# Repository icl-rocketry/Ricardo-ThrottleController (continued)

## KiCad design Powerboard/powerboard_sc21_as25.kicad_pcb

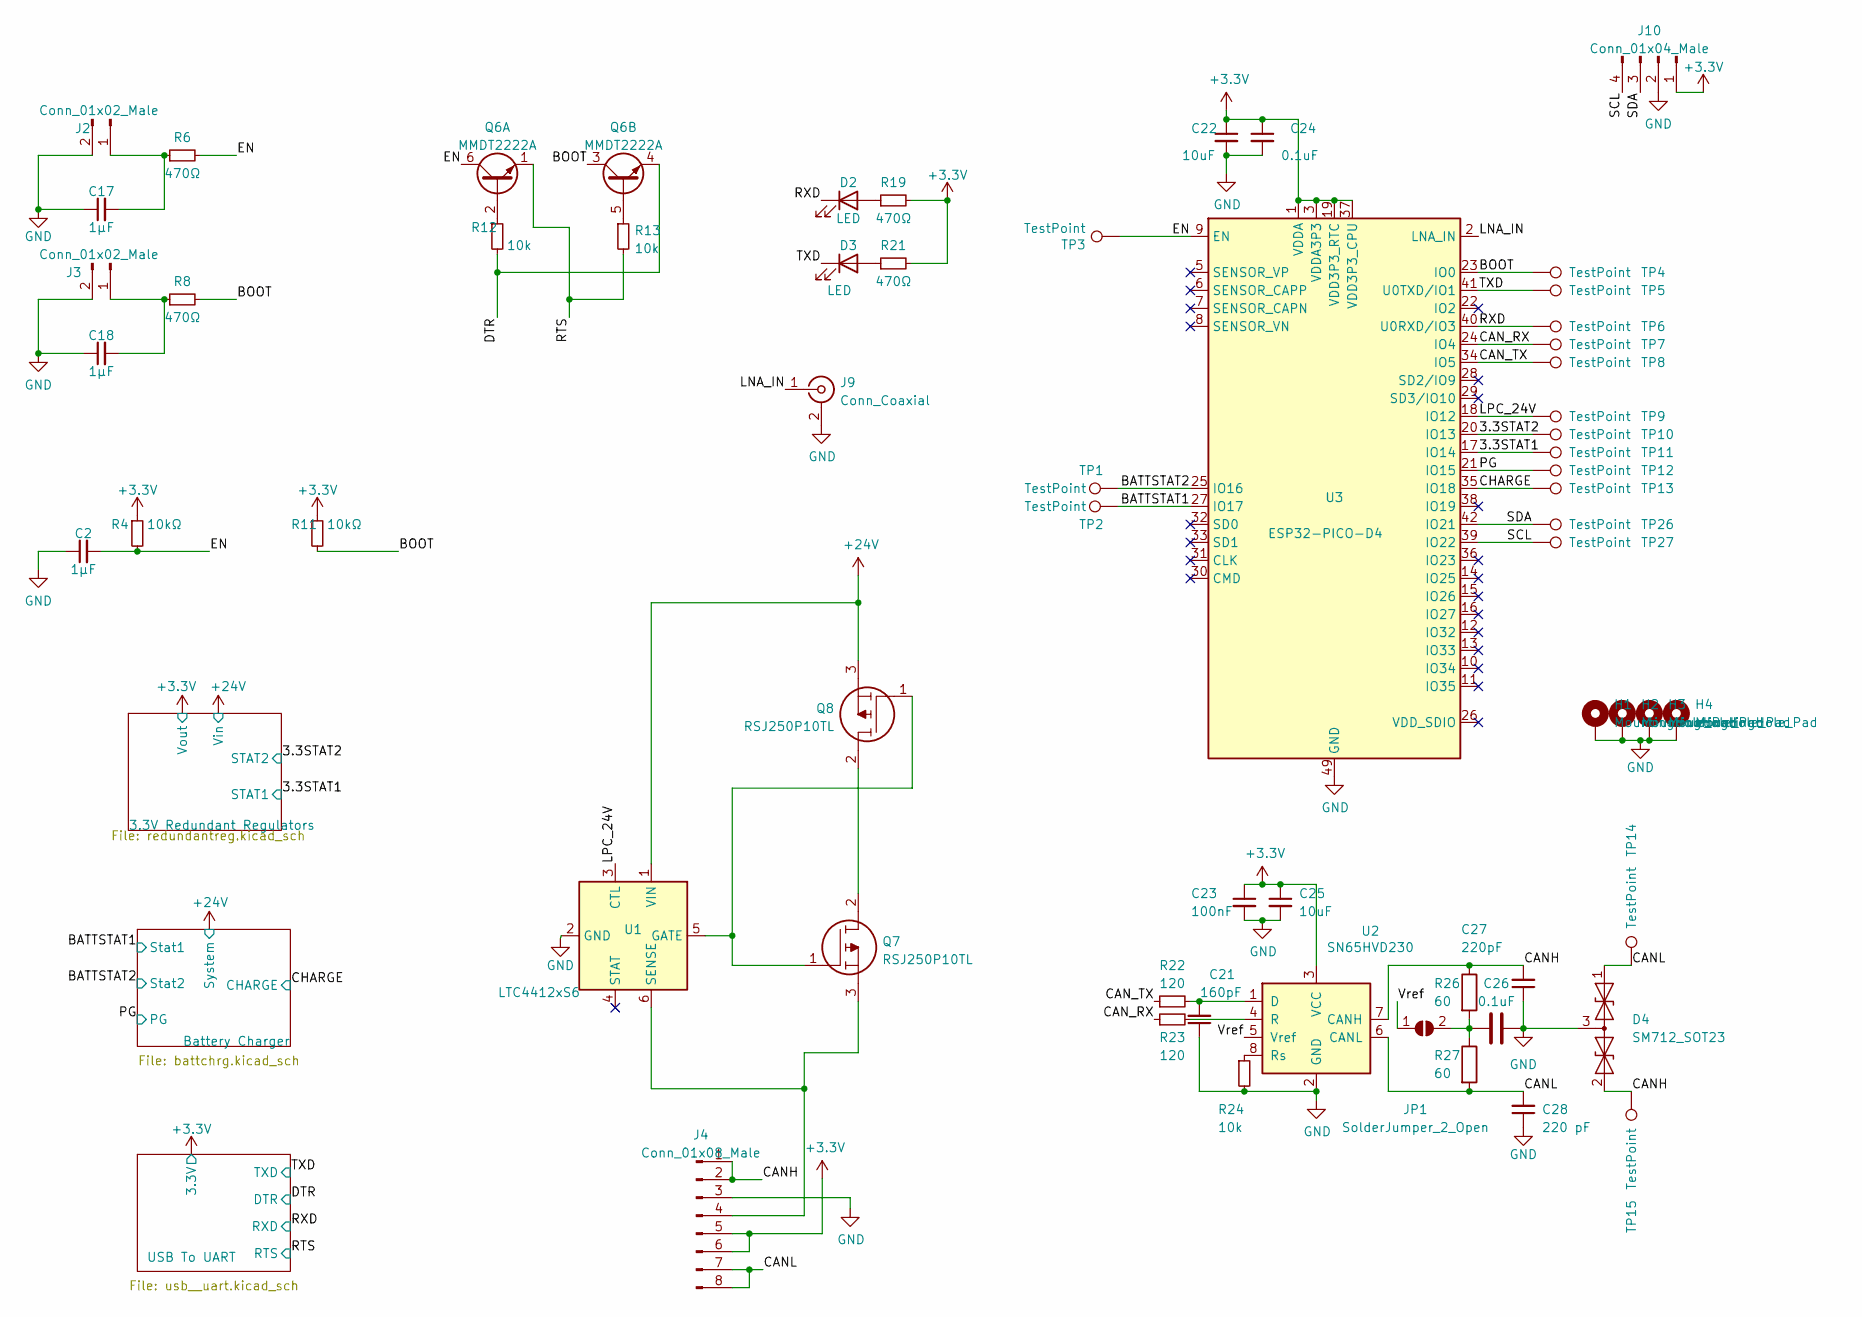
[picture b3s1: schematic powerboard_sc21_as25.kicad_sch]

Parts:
C2, C17, C18: 1μF; C_0603_1608Metric
C21: 160pF; C_0603_1608Metric
C22, C25: 10uF; C_0805_2012Metric
C23: 100nF; C_0603_1608Metric
C24, C26: 0.1uF; C_0603_1608Metric
C27: 220pF; C_0603_1608Metric
C28: 220 pF; C_0603_1608Metric
D2, D3: LED; LED_0603_1608Metric
D4: SM712_SOT23; SOT-23
H1, H2, H3, H4: MountingHole_Pad; MountingHole_3.2mm_M3_DIN965_Pad
J2, J3: Conn_01x02_Male; PinHeader_1x02_P2.54mm_Vertical
J4: Conn_01x08_Male; Molex_Mini-Fit_Jr_5566-08A_2x04_P4.20mm_Vertical
J9: Conn_Coaxial; U.FL_Molex_MCRF_73412-0110_Vertical
J10: Conn_01x04_Male; JST_XH_B4B-XH-AM_1x04_P2.50mm_Vertical
JP1: SolderJumper_2_Open; SolderJumper-2_P1.3mm_Open_RoundedPad1.0x1.5mm
Q6: MMDT2222A; SOT-363_SC-70-6
Q7, Q8: RSJ250P10TL; TO-263-3_TabPin2; Manufacturer_Part_Number RSJ250P10TL; Mouser Part Number 755-RSJ250P10TL
R4, R11: 10kΩ; R_0603_1608Metric
R6, R8, R19, R21: 470Ω; R_0603_1608Metric
R12, R13, R24: 10k; R_0603_1608Metric
R22, R23: 120; R_0603_1608Metric
R26, R27: 60; R_0603_1608Metric
TP1, TP2, TP3, TP4, TP5, TP6, TP7, TP8, TP9, TP10, TP11, TP12, TP13, TP14, TP15, TP26, TP27: TestPoint; TestPoint_Pad_D1.0mm
U1: LTC4412xS6; TSOT-23-6
U2: SN65HVD230; SOIC-8_3.9x4.9mm_P1.27mm
U3: ESP32-PICO-D4; QFN-48-1EP_7x7mm_P0.5mm_EP5.3x5.3mm

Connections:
+3V3: C22.1, C23.1, C24.1, C25.1, J4.5, J4.6, J10.1, R4.1, R11.1, R19.2, R21.2, U2.3 (VCC), U3.1 (VDDA), U3.3 (VDDA3P3), U3.4 (VDDA3P3), U3.19 (VDD3P3_RTC), U3.37 (VDD3P3_CPU), U3.43 (VDDA), U3.46 (VDDA); also elsewhere on the board
+24V: Q8.3, U1.1 (VIN); also elsewhere on the board
/3.3STAT1: TP11.1, U3.17 (IO14); also elsewhere on the board
/3.3STAT2: TP10.1, U3.20 (IO13); also elsewhere on the board
/BATTSTAT1: TP2.1, U3.27 (IO17); also elsewhere on the board
/BATTSTAT2: TP1.1, U3.25 (IO16); also elsewhere on the board
/BOOT: Q6.3 (C2), R8.2, R11.2, TP4.1, U3.23 (IO0)
/CANH: C27.2, D4.2 (A2), J4.1, J4.2, R26.1, TP15.1, U2.7 (CANH)
/CANL: C28.2, D4.1 (A1), J4.7, J4.8, R27.2, TP14.1, U2.6 (CANL)
/CAN_RX: R23.1, TP7.1, U3.24 (IO4)
/CAN_TX: R22.1, TP8.1, U3.34 (IO5)
/CHARGE: TP13.1, U3.35 (IO18); also elsewhere on the board
/DTR: Q6.4 (E2), R12.2; also elsewhere on the board
/EN: C2.2, Q6.6 (C1), R4.2, R6.2, TP3.1, U3.9 (EN)
/LNA_IN: J9.1 (In), U3.2 (LNA_IN)
/LPC_24V: TP9.1, U1.3 (CTL), U3.18 (IO12)
/PG: TP12.1, U3.21 (IO15); also elsewhere on the board
/RTS: Q6.1 (E1), R13.2; also elsewhere on the board
/RXD: D2.1 (K), TP6.1, U3.40 (U0RXD/IO3); also elsewhere on the board
/SCL: J10.4, TP27.1, U3.39 (IO22)
/SDA: J10.3, TP26.1, U3.42 (IO21)
/TXD: D3.1 (K), TP5.1, U3.41 (U0TXD/IO1); also elsewhere on the board
/Vref: JP1.1 (A), U2.5 (Vref)
GND: C2.1, C17.1, C18.1, C21.1, C22.2, C23.2, C24.2, C25.2, C26.2, C27.1, C28.1, D4.3 (common), H1.1, H2.1, H3.1, H4.1, J2.2, J3.2, J4.3, J9.2 (Ext), J10.2, R24.2, U1.2 (GND), U2.2 (GND), U3.49 (GND); also elsewhere on the board
unnamed: C17.2, J2.1, R6.1
unnamed: C18.2, J3.1, R8.1
unnamed: C21.2, R22.2, U2.1 (D)
unnamed: C26.1, JP1.2 (B), R26.2, R27.1
unnamed: D2.2 (A), R19.1
unnamed: D3.2 (A), R21.1
unnamed: J4.4, Q7.3, U1.6 (SENSE)
unnamed: Q6.2 (B1), R12.1
unnamed: Q6.5 (B2), R13.1
unnamed: Q7.1, Q8.1, U1.5 (GATE)
unnamed: Q7.2, Q8.2
unnamed: R23.2, U2.4 (R)
unnamed: R24.1, U2.8 (Rs)

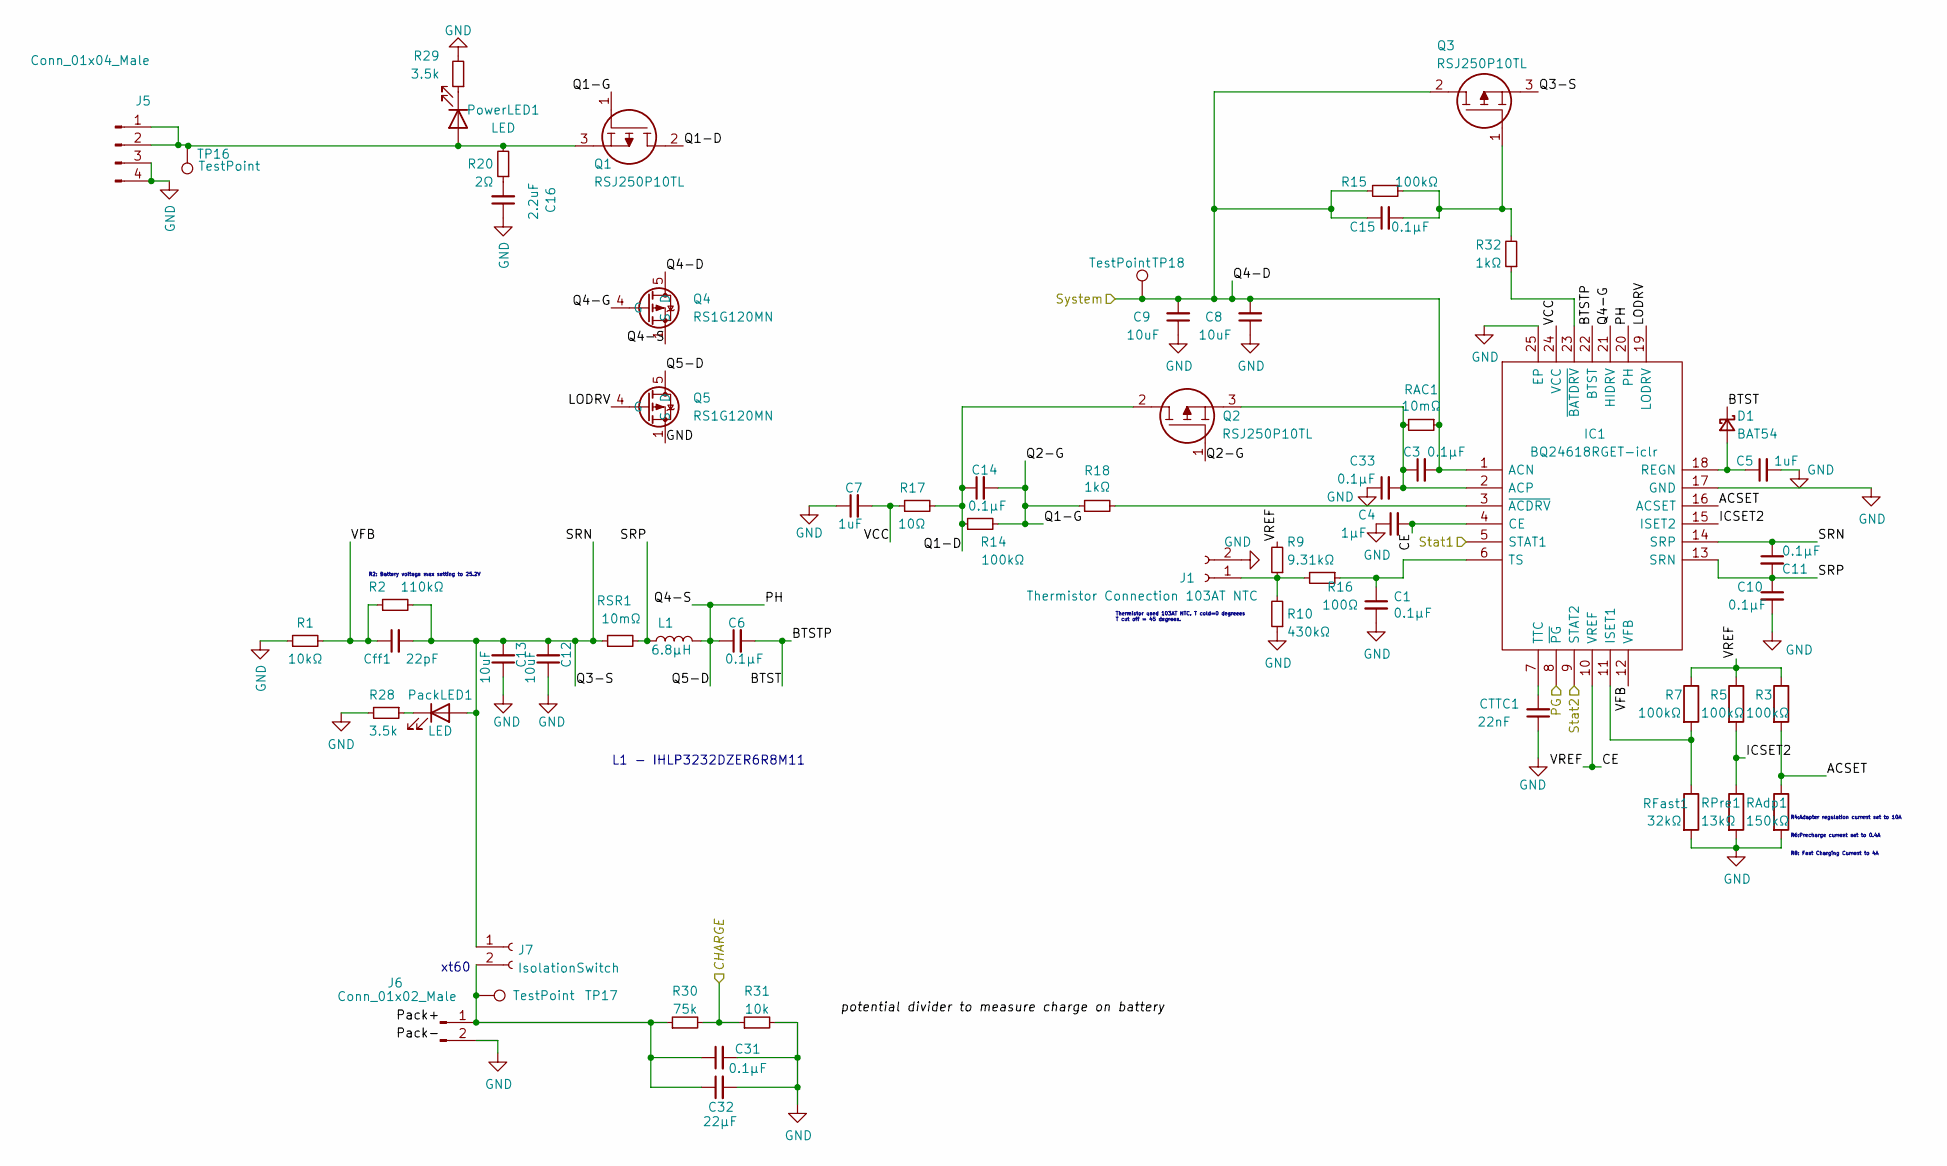
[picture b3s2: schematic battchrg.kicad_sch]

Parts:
C1, C3, C10, C11, C31, C33: 0.1μF; C_0603_1608Metric
C4: 1μF; C_0603_1608Metric
C5, C7: 1uF; C_0603_1608Metric
C6, C14, C15: 0.1µF; C_0603_1608Metric
C8, C9, C12, C13: 10uF; C_0805_2012Metric
C16: 2.2uF; C_0805_2012Metric
C32: 22μF; C_1210_3225Metric
CTTC1: 22nF; C_0603_1608Metric
Cff1: 22pF; C_0603_1608Metric
D1: BAT54; D_SOT-23_ANK
IC1: BQ24618RGET-iclr; VQFN-24-1EP_4x4mm_P0.5mm_EP2.45x2.45mm; Manufacturer_Part_Number BQ24618RGET; Mouser Part Number 595-BQ24618RGET
J1: Thermistor Connection 103AT NTC; JST_XH_B2B-XH-AM_1x02_P2.50mm_Vertical
J5: Conn_01x04_Male; Molex_Mini-Fit_Jr_5566-04A_2x02_P4.20mm_Vertical
J6: Conn_01x02_Male; AMASS_XT60-M_1x02_P7.20mm_Vertical
J7: IsolationSwitch; AMASS_XT60-M_1x02_P7.20mm_Vertical
L1: 6.8µH; INDM8681X400N
PackLED1: LED; LED_0603_1608Metric
PowerLED1: LED; LED_0603_1608Metric
Q1, Q2, Q3: RSJ250P10TL; TO-263-3_TabPin2; Manufacturer_Part_Number RSJ250P10TL; Mouser Part Number 755-RSJ250P10TL
Q4, Q5: RS1G120MN; HSOP-8-1EP_3.9x4.9mm_P1.27mm_EP2.41x3.1mm
R1: 10kΩ; R_0603_1608Metric
R2: 110kΩ; R_0603_1608Metric
R3, R5, R7, R14, R15: 100kΩ; R_0603_1608Metric
R9: 9.31kΩ; R_0603_1608Metric
R10: 430kΩ; R_0603_1608Metric
R16: 100Ω; R_0603_1608Metric
R17: 10Ω; R_0603_1608Metric
R18, R32: 1kΩ; R_0603_1608Metric
R20: 2Ω; R_0603_1608Metric
R28, R29: 3.5k; R_0603_1608Metric
R30: 75k; R_0603_1608Metric
R31: 10k; R_0603_1608Metric
RAC1: 10mΩ; R_0603_1608Metric
RAdp1: 150kΩ; R_0603_1608Metric
RFast1: 32kΩ; R_0603_1608Metric
RPre1: 13kΩ; R_0603_1608Metric
RSR1: 10mΩ; R_0603_1608Metric
TP16, TP17, TP18: TestPoint; TestPoint_Pad_D1.0mm

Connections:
+24V: C3.2, C8.2, C9.2, C15.1, IC1.1 (ACN), Q3.2, Q4.5 (D), Q4.6 (D), Q4.7 (D), Q4.8 (D), Q4.9 (D), R15.2, RAC1.1, TP18.1; also elsewhere on the board
/BATTSTAT1: IC1.5 (STAT1); also elsewhere on the board
/BATTSTAT2: IC1.9 (STAT2); also elsewhere on the board
/Battery Charger/ACSET: IC1.16 (ACSET), R3.2, RAdp1.1
/Battery Charger/BTST: C6.2, D1.1 (K), IC1.22 (BTST)
/Battery Charger/CE: C4.2, IC1.4 (CE), IC1.10 (VREF), R3.1, R5.1, R7.1, R9.2
/Battery Charger/LODRV: IC1.19 (LODRV), Q5.4 (G)
/Battery Charger/PH: C6.1, IC1.20 (PH), L1.2, Q4.1 (S), Q4.2 (S), Q4.3 (S), Q5.5 (D), Q5.6 (D), Q5.7 (D), Q5.8 (D), Q5.9 (D)
/Battery Charger/Q1-D: C14.1, Q1.2, Q2.2, R14.1, R17.2
/Battery Charger/Q1-G: C14.2, Q1.1, Q2.1, R14.2, R18.1
/Battery Charger/Q3-S: C11.1, C12.2, C13.2, Cff1.2, IC1.14 (SRP), J7.1, PackLED1.2 (A), Q3.3, R2.2, RSR1.1
/Battery Charger/Q4-G: IC1.21 (HIDRV), Q4.4 (G)
/Battery Charger/SRP: C10.1, C11.2, IC1.13 (SRN), L1.1, RSR1.2
/Battery Charger/VCC: C7.2, IC1.24 (VCC), R17.1
/Battery Charger/VFB: Cff1.1, IC1.12 (VFB), R1.2, R2.1
/CHARGE: R30.2, R31.1; also elsewhere on the board
/PG: IC1.8 (~PG); also elsewhere on the board
GND: C1.2, C4.1, C5.2, C7.1, C8.1, C9.1, C10.2, C12.1, C13.1, C16.1, C31.2, C32.2, C33.1, CTTC1.1, IC1.17 (GND), IC1.25 (EP), J1.2, J5.3, J5.4, J6.2, Q5.1 (S), Q5.2 (S), Q5.3 (S), R1.1, R10.1, R28.2, R29.2, R31.2, RAdp1.2, RFast1.2, RPre1.2; also elsewhere on the board
unnamed: C1.1, IC1.6 (TS), R16.1
unnamed: C3.1, C33.2, IC1.2 (ACP), Q2.3, RAC1.2
unnamed: C5.1, D1.2 (A), IC1.18 (REGN)
unnamed: C15.2, Q3.1, R15.1, R32.2
unnamed: C16.2, R20.1
unnamed: C31.1, C32.1, J6.1, J7.2, R30.1, TP17.1
unnamed: CTTC1.2, IC1.7 (TTC)
unnamed: IC1.3 (~ACDRV), R18.2
unnamed: IC1.11 (ISET1), R7.2, RFast1.1
unnamed: IC1.23 (~BATDRV), R32.1
unnamed: J1.1, R9.1, R10.2, R16.2
unnamed: J5.1, J5.2, TP16.1
unnamed: PackLED1.1 (K), R28.1
unnamed: PowerLED1.1 (K), R29.1
unnamed: PowerLED1.2 (A), Q1.3, R20.2

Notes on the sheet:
R2: Battery voltage max setting to 25.2V
R4:Adapter regulation current set to 10A
L1 - IHLP3232DZER6R8M11
R8: Fast Charging Current to 4A
Thermistor used 103AT NTC. T cold=0 degreees T cut off = 45 degrees.
R6:Precharge current set to 0.4A
xt60

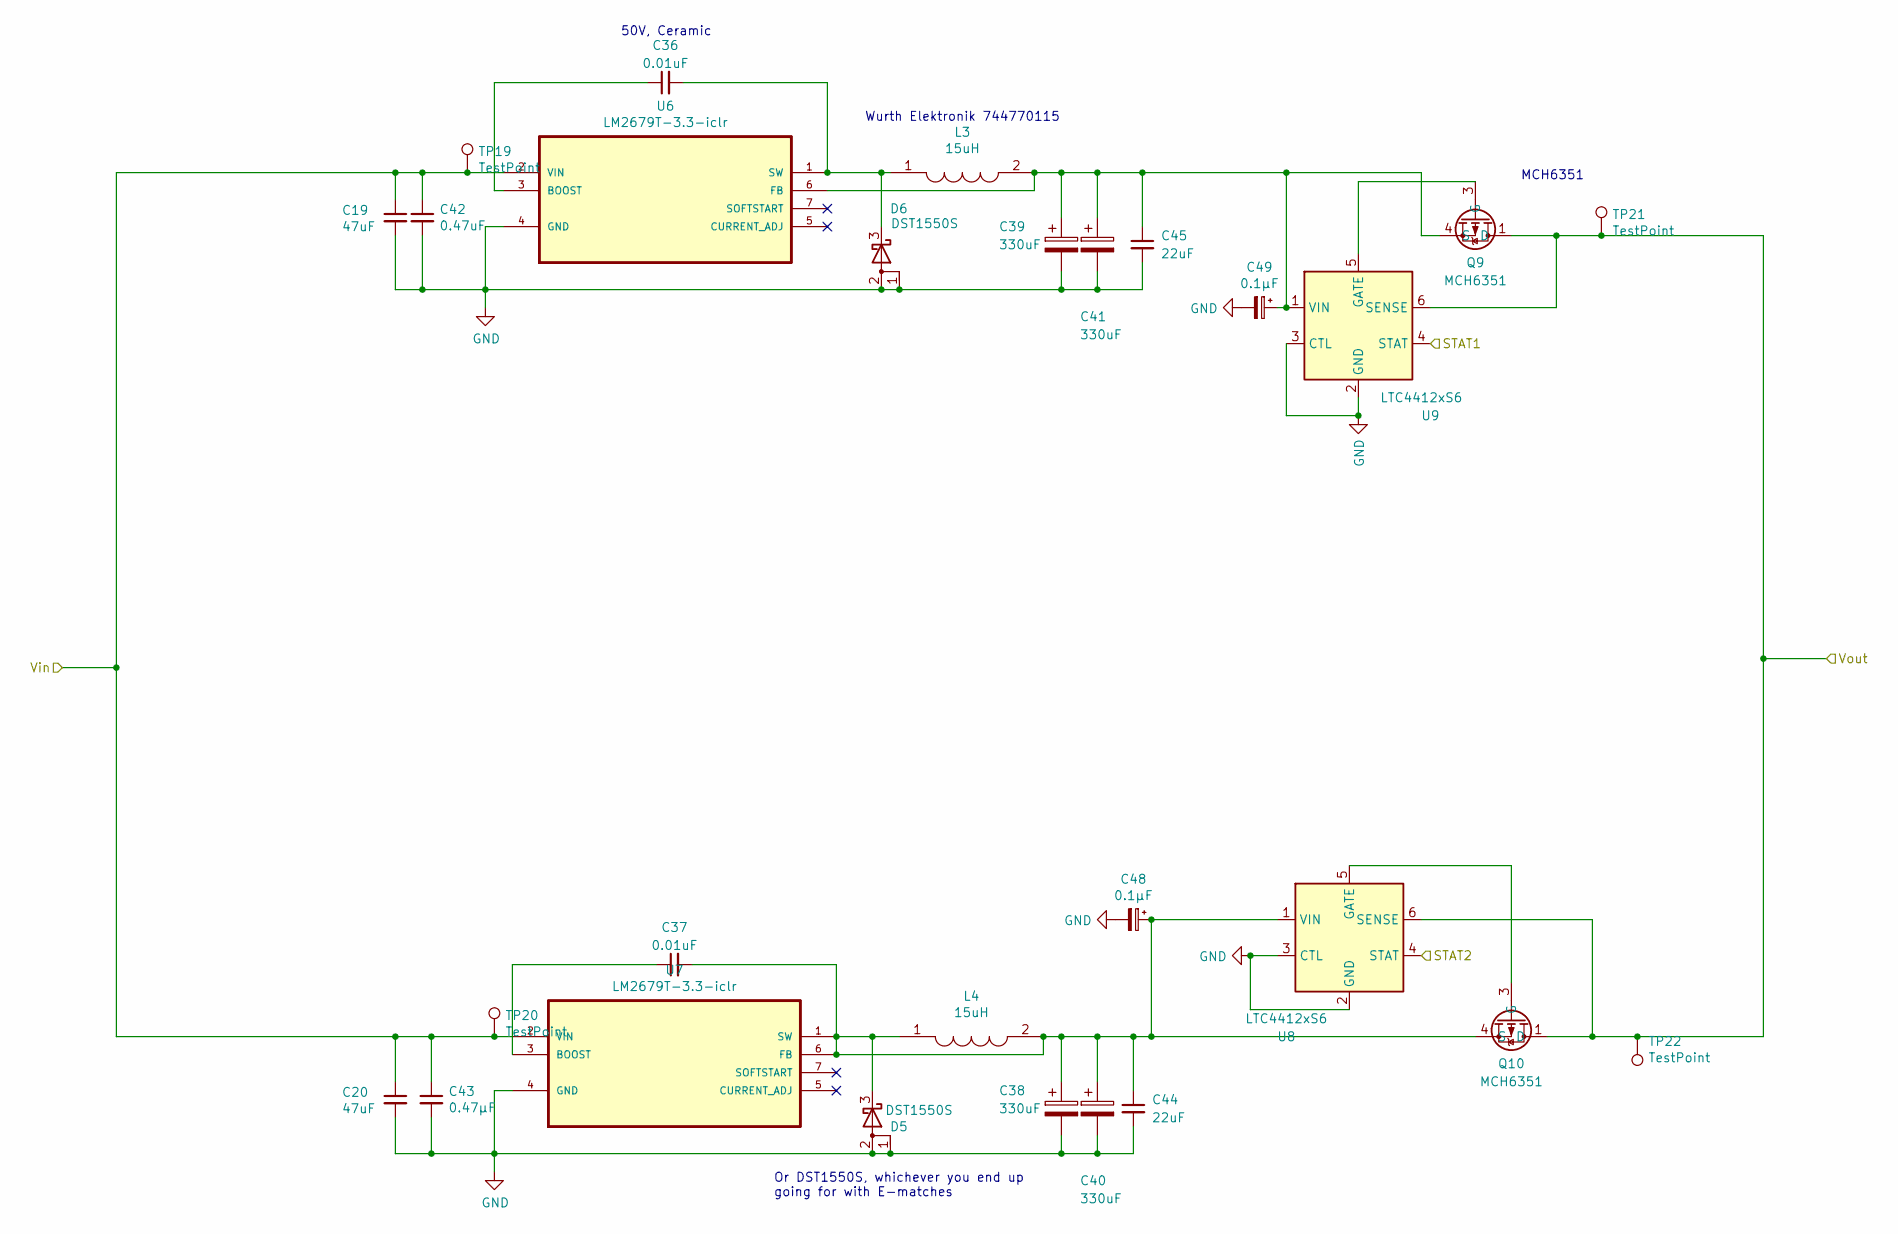
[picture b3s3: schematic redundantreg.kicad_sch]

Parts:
C19, C20: 47uF; C_2220_5650Metric
C36, C37: 0.01uF; C_0603_1608Metric
C38, C39, C40, C41: 330uF; CP_EIA-7343-30_AVX-N
C42: 0.47uF; C_0805_2012Metric
C43: 0.47μF; C_0805_2012Metric
C44, C45: 22uF; C_0603_1608Metric
C48, C49: 0.1µF; C_0603_1608Metric
D5, D6: DST1550S; TO-277B
L3, L4: 15uH; L_12x12mm_H8mm; Manufacturer_Part_Number P0846SNL; Mouser Part Number 673-P0846SNL
Q9, Q10: MCH6351; SOT-363_SC-70-6
TP19, TP20, TP21, TP22: TestPoint; TestPoint_Pad_D1.0mm
U6, U7: LM2679T-3.3-iclr; TO-263-7_TabPin4; MPN LM2679T-3.3
U8, U9: LTC4412xS6; TSOT-23-6

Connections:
+3V3: Q9.1 (D), Q9.2 (D), Q9.5 (D), Q9.6 (D), Q10.1 (D), Q10.2 (D), Q10.5 (D), Q10.6 (D), TP21.1, TP22.1, U8.6 (SENSE), U9.6 (SENSE); also elsewhere on the board
+24V: C19.1, C20.1, C42.1, C43.1, TP19.1, TP20.1, U6.2 (VIN), U7.2 (VIN); also elsewhere on the board
/3.3STAT1: U9.4 (STAT); also elsewhere on the board
/3.3STAT2: U8.4 (STAT); also elsewhere on the board
GND: C19.2, C20.2, C38.2, C39.2, C40.2, C41.2, C42.2, C43.2, C44.2, C45.2, C48.2, C49.2, D5.1 (A), D5.2 (A), D6.1 (A), D6.2 (A), U6.4 (GND), U7.4 (GND), U8.2 (GND), U8.3 (CTL), U9.2 (GND), U9.3 (CTL); also elsewhere on the board
unnamed: C36.1, U6.3 (BOOST)
unnamed: C36.2, D6.3 (K), L3.1, U6.1 (SW)
unnamed: C37.1, U7.3 (BOOST)
unnamed: C37.2, C38.1, C40.1, C44.1, C48.1, D5.3 (K), L4.1, L4.2, Q10.4 (S), U7.1 (SW), U7.6 (FB), U8.1 (VIN)
unnamed: C39.1, C41.1, C45.1, C49.1, L3.2, Q9.4 (S), U6.6 (FB), U9.1 (VIN)
unnamed: Q9.3 (G), U9.5 (GATE)
unnamed: Q10.3 (G), U8.5 (GATE)

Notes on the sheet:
Wurth Elektronik 744770115
50V, Ceramic
Or DST1550S, whichever you end up going for with E-matches
MCH6351

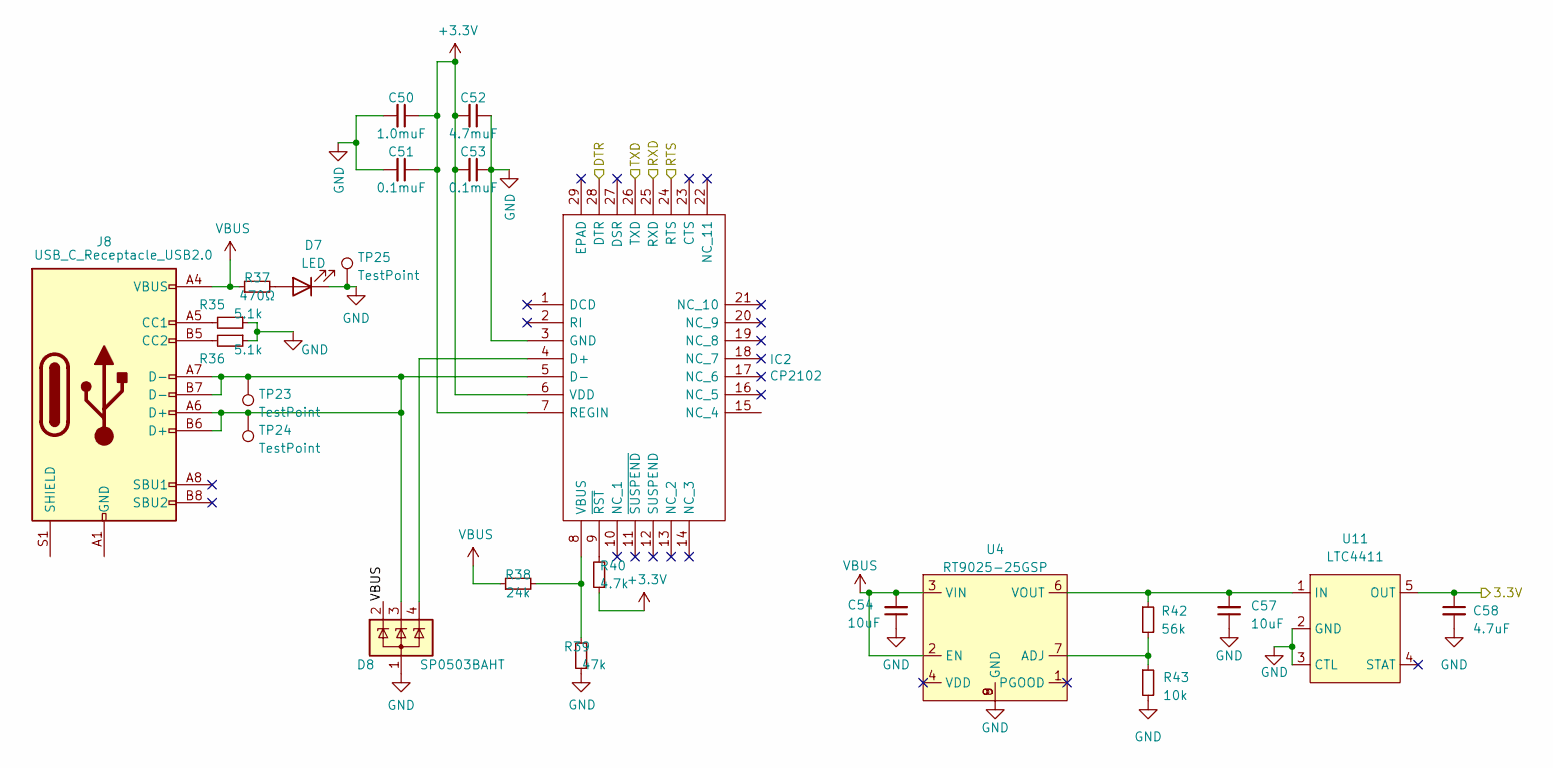
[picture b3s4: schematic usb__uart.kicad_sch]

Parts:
C50: 1.0muF; C_0603_1608Metric
C51, C53: 0.1muF; C_0603_1608Metric
C52: 4.7muF; C_0603_1608Metric
C54, C57: 10uF; C_0805_2012Metric
C58: 4.7uF; C_0603_1608Metric
D7: LED; LED_0603_1608Metric
D8: SP0503BAHT; SOT-143
IC2: CP2102; QFN28G_0.5-5X5MM; Manufacturer_Part_Number CP2102; Mouser Part Number 634-CP2102
J8: USB_C_Receptacle_USB2.0; USB_C_Receptacle_GCT_USB4085
R35, R36: 5.1k; R_0603_1608Metric
R37: 470Ω; R_0603_1608Metric
R38: 24k; R_0603_1608Metric
R39: 47k; R_0603_1608Metric
R40: 4.7k; R_0603_1608Metric
R42: 56k; R_0603_1608Metric
R43: 10k; R_0603_1608Metric
TP23, TP24, TP25: TestPoint; TestPoint_Pad_D1.0mm
U4: RT9025-25GSP; SOIC127P599X175-9N
U11: LTC4411; SOT-23-5

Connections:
+3V3: C50.1, C51.1, C52.2, C53.2, C58.1, IC2.6 (VDD), IC2.7 (REGIN), R40.1, U11.5 (OUT); also elsewhere on the board
/DTR: IC2.28 (DTR); also elsewhere on the board
/RTS: IC2.24 (RTS); also elsewhere on the board
/RXD: IC2.25 (RXD); also elsewhere on the board
/TXD: IC2.26 (TXD); also elsewhere on the board
GND: C50.2, C51.2, C52.1, C53.1, C54.1, C57.1, C58.2, D7.1 (K), D8.1 (A), IC2.3 (GND), R35.1, R36.1, R39.1, R43.2, TP25.1, U4.8 (GND), U4.9 (GND), U11.2 (GND), U11.3 (CTL); also elsewhere on the board
unnamed: C57.2, R42.1, U4.6 (VOUT), U11.1 (IN)
unnamed: D7.2 (A), R37.2
unnamed: D8.3 (K), IC2.5 (D-), J8.A6 (D+), J8.A7 (D-), J8.B6 (D+), J8.B7 (D-), TP23.1, TP24.1
unnamed: D8.4 (K), IC2.4 (D+)
unnamed: IC2.8 (VBUS), R38.2, R39.2
unnamed: IC2.9 (~RST), R40.2
unnamed: J8.A1 (GND), J8.A12 (GND), J8.B1 (GND), J8.B12 (GND)
unnamed: J8.A5 (CC1), R35.2
unnamed: J8.B5 (CC2), R36.2
unnamed: R42.2, R43.1, U4.7 (ADJ)
VBUS: C54.2, D8.2 (K), J8.A4 (VBUS), J8.A9 (VBUS), J8.B4 (VBUS), J8.B9 (VBUS), R37.1, R38.1, U4.2 (EN), U4.3 (VIN)

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
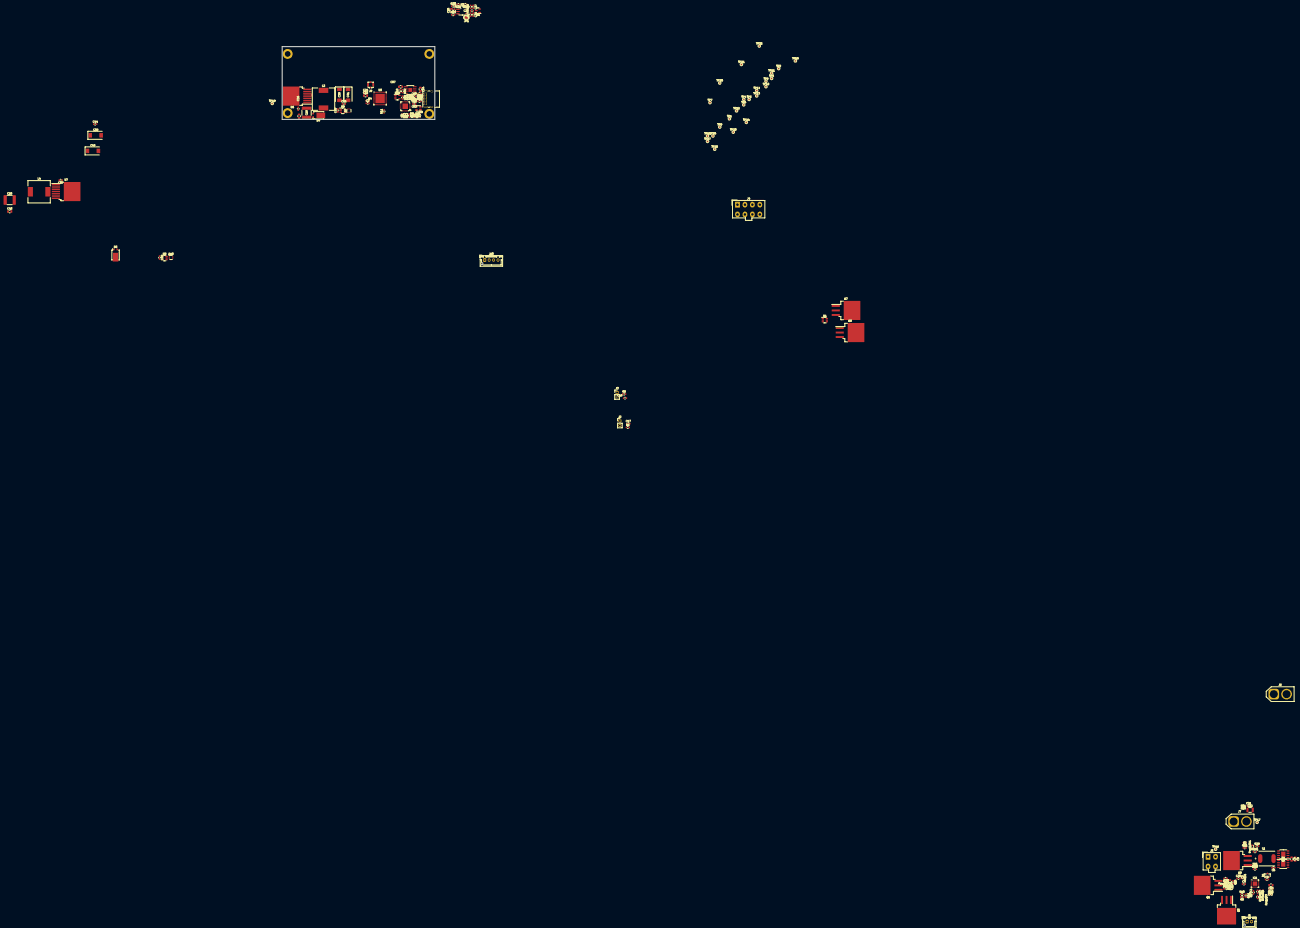
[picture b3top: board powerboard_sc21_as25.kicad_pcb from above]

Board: 4 copper layers, 86.0 x 41.0 mm, 172 parts (0 on the bottom side), 83 nets.

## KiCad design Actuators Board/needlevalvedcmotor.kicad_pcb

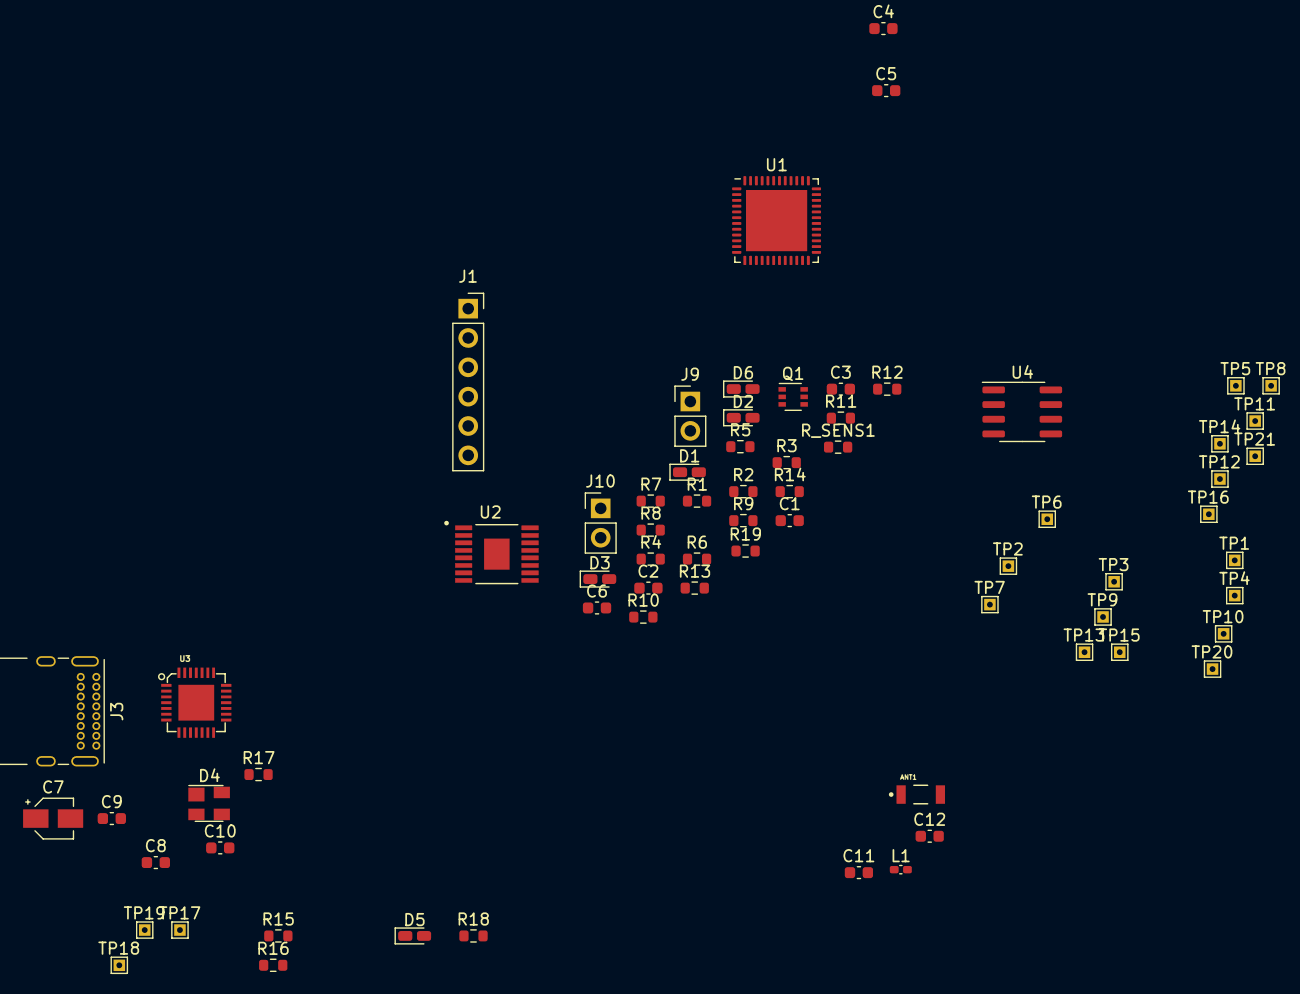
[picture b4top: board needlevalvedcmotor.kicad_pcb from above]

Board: 2 copper layers, 70 parts (0 on the bottom side), 39 nets, no tracks yet.

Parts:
ANT1: AMCA31-2R450G-S1F-T3; ANT_AMCA31-2R450G-S1F-T3
C1, C2, C3, C4, C9, C10: 0.1uF; C_0603_1608Metric
C5: 10uF; C_0603_1608Metric
C6: 1uF; C_0603_1608Metric
C7: 4.7uF; CP_Elec_3x5.3
C8: 1.0uF; C_0603_1608Metric
C11: 1.2pF; C_0603_1608Metric
C12: 1.5pF; C_0603_1608Metric
D1: 24V LED; LED_0603_1608Metric_Castellated
D2: RX_LED; LED_0603_1608Metric_Castellated
D3: TX_LED; LED_0603_1608Metric_Castellated
D4: SP0503BAHT; SOT-143
D5: USB_LED; LED_0603_1608Metric_Castellated
D6: 3.3V LED; LED_0603_1608Metric_Castellated
J1: Conn_01x06_Male; PinSocket_1x06_P2.54mm_Vertical
J3: USB_C_Receptacle_USB2.0; USB_C_Receptacle_GCT_USB4085
J9, J10: Conn_01x02_Male; PinHeader_1x02_P2.54mm_Vertical
L1: LQG15WZ1N8B02D; L_0402_1005Metric_Pad0.77x0.64mm_HandSolder
Q1: MMDT2222A; SOT-363_SC-70-6
R1, R2, R7, R8: 10K; R_0603_1608Metric
R3, R4, R5, R9, R10, R11, R14, R18: 470; R_0603_1608Metric
R6, R12: 1k; R_0603_1608Metric
R13: 10k; R_0603_1608Metric
R15, R16: 5.1k; R_0603_1608Metric
R17: 4.7k; R_0603_1608Metric
R19: 1.1k; R_0603_1608Metric
R_SENS1: 0.1; R_0603_1608Metric
TP1, TP2, TP3, TP4, TP5, TP6, TP7, TP8, TP9, TP10, TP11, TP12, TP13, TP14, TP15, TP16, TP17, TP18, TP19, TP20, TP21: TestPoint; TestPoint_THTPad_1.0x1.0mm_Drill0.5mm
U1: ESP32-PICO-D4; QFN-48-1EP_7x7mm_P0.5mm_EP5.3x5.3mm
U2: MAX14871EUE+; SOP65P637X110-16N
U3: INTERFACE-CP2102-GMR(QFN28); QFN28G_0.5-5X5MM
U4: SN65HVD230; SOIC-8_3.9x4.9mm_P1.27mm

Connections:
+3V3: C4.1, C5.1, C7.2, C9.2, J1.4, R7.1, R8.1, R10.1, R11.1, R13.1, R14.2, R17.1, U2.8, U3.6, U4.3
+24V: C6.1, R12.2, U2.4, U2.13
/BOOT: Q1.3, R8.2, R9.1, TP9.1, U1.23
/CAN_HIGH: TP6.1, U4.7
/CAN_LOW: TP7.1, U4.6
/CAN_RX: TP20.1, U1.13, U4.4
/CAN_TX: TP21.1, U1.12, U4.1
/COMM: R_SENS1.1, U2.1, U2.5, U2.16
/DTR: Q1.4, R1.2, TP4.1, U3.28
/EN: C2.1, Q1.6, R5.1, R7.2, TP5.1, U1.9
/FAULT: R13.2, TP15.1, TP16.1, U1.35, U2.10
/Hall1: J1.5, TP13.1, U1.34
/Hall2: J1.6, TP12.1, U1.24
/LNA_IN: C11.1, L1.1, TP8.1, U1.2
/Motor+: J1.1, U2.2, U2.3
/Motor-: J1.2, U2.14, U2.15
/PWM: TP14.1, U1.18, U2.6
/RTS: Q1.1, R2.2, TP1.1, U3.24
/RXD: D2.1, TP2.1, TP10.1, U1.41, U3.25
/TXD: D3.1, TP3.1, TP11.1, U1.40, U3.26
/USB -> UART/Data+: D4.4, J3.A6, J3.B6, TP18.1, U3.4
/USB -> UART/Data-: D4.3, J3.A7, J3.B7, TP17.1, U3.5
GND: C1.2, C2.2, C3.2, C4.2, C5.2, C6.2, C7.1, C8.1, C9.1, C10.1, C11.2, C12.2, D1.1, D4.1, D5.1, D6.1, J1.3, J3.A1, J3.A12, J3.B1, J3.B12, J3.S1, J9.2, J10.2, R3.2, R4.1, R4.2, R6.1, R15.2, R16.1, R19.2, R_SENS1.2, U1.1, U1.3, U1.4, U1.19, U1.37, U1.43, U1.46, U1.49, U2.11, U2.17, U3.3, U4.2, U4.8
unnamed: ANT1.1, C12.1, L1.2
unnamed: C1.1, J9.1, R5.2
unnamed: C3.1, J10.1, R9.2
unnamed: D1.2, R3.1
unnamed: D2.2, R10.2
unnamed: D3.2, R11.2
unnamed: D5.2, R18.2
unnamed: D6.2, R14.1
unnamed: J3.A5, R15.1
unnamed: J3.B5, R16.2
unnamed: Q1.2, R1.1
unnamed: Q1.5, R2.1
unnamed: R6.2, R12.1
unnamed: R17.2, U3.9
unnamed: R19.1, U2.12
VBUS: C8.2, C10.2, D4.2, J3.A4, J3.A9, J3.B4, J3.B9, R18.1, TP19.1, U3.7, U3.8

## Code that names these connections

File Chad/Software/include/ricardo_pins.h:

/*
**********************
* PINS               *
**********************
 */
#pragma once


static constexpr int TxCan = 14;
static constexpr int RxCan = 27;

// static constexpr int SolEN = 9;

static constexpr int HBridgeDIR2 = 25;
static constexpr int HBridgeDIR1 = 26;

static constexpr int ServoPWM = 32;
// static constexpr int ES1GPIO = 35;
static constexpr int ssrPin = 9;

static constexpr int forwardButton = 35;
static constexpr int backButton = 37;

// static constexpr int ServoPWM = 9

// static constexpr int ES1GPIO = 34;
// static constexpr int ES2GPIO = 17;
